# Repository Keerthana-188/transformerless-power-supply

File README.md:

# transformerless-power-supply
This project is a PCB design for a **Transformerless Power Supply** created using KiCad.  
It provides a compact and cost-effective way to power low-current DC circuits directly from AC mains without using bulky transformers.

# Features
Compact PCB layout using through-hole components
- Converts AC to regulated DC using:
  - Capacitor dropper (C4)
  - Full-wave bridge rectifier (D1–D4)
  - Filtering and regulation using LM7805 or LM7812
  - Protection diodes and discharge resistors
  - Indicator LED for output status

## Comparison: Transformerless vs. Conventional Power Supply

| Feature                        | Transformerless Power Supply                        | Conventional Power Supply                            |
|-------------------------------|-----------------------------------------------------|------------------------------------------------------|
| **Size & Weight**             | Very compact and lightweight                        | Bulky due to iron-core transformer                   |
| **Cost**                      | Low cost – fewer and cheaper components             | Higher cost due to transformer and large components  |
| **Efficiency (Low Power Load)** | High for small loads                                 | Moderate (some loss in transformer)                  |
| **Power Output Capacity**     | Suitable only for **low current** applications      | Can provide high current based on transformer rating |
| **Safety**                    | Risky if not handled properly (AC mains exposed)    | Safer due to isolation, especially for beginners     |
| **Applications**              | LED drivers, small control circuits, chargers       | Audio amplifiers, adapters, regulated power supplies |

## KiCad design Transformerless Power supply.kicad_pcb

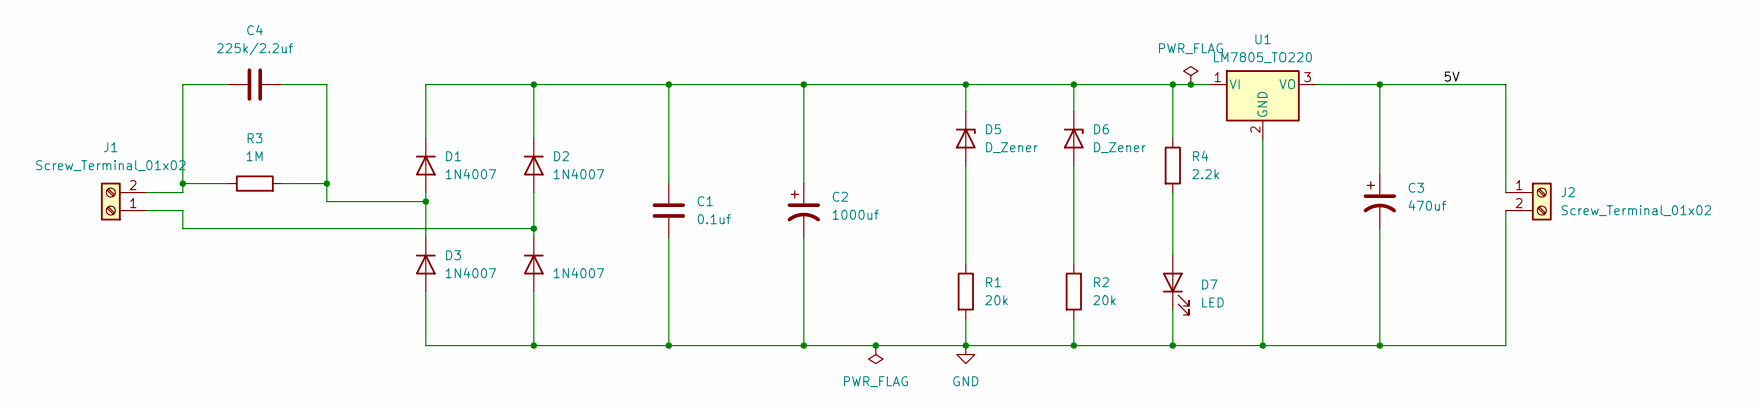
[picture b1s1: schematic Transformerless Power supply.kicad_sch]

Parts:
C1: 0.1uf; C_Disc_D4.7mm_W2.5mm_P5.00mm
C2: 1000uf; CP_Radial_D10.0mm_P5.00mm
C3: 470uf; CP_Radial_D10.0mm_P3.80mm
C4: 225k/2.2uf; C_Rect_L18.0mm_W6.0mm_P15.00mm_FKS3_FKP3
D1, D2, D3, D4: 1N4007; D_DO-41_SOD81_P10.16mm_Horizontal
D5, D6: D_Zener; D_A-405_P7.62mm_Horizontal
D7: LED; LED_D5.0mm
J1, J2: Screw_Terminal_01x02; TerminalBlock_bornier-2_P5.08mm
R1, R2: 20k; R_Axial_DIN0207_L6.3mm_D2.5mm_P7.62mm_Horizontal
R3: 1M; R_Axial_DIN0207_L6.3mm_D2.5mm_P7.62mm_Horizontal
R4: 2.2k; R_Axial_DIN0207_L6.3mm_D2.5mm_P7.62mm_Horizontal
U1: LM7805_TO220; TO-220-3_Vertical

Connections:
/5V: C3.1, J2.1, U1.3 (VO)
GND: C1.2, C2.2, C3.2, D3.2 (A), D4.2 (A), D7.1 (K), J2.2, R1.2, R2.2, U1.2 (GND)
unnamed: C4.2, D1.2 (A), D3.1 (K), R3.2
unnamed: C1.1, C2.1, D1.1 (K), D2.1 (K), D5.1 (K), D6.1 (K), R4.1, U1.1 (VI)
unnamed: D2.2 (A), D4.1 (K), J1.1
unnamed: D5.2 (A), R1.1
unnamed: D6.2 (A), R2.1
unnamed: D7.2 (A), R4.2
unnamed: C4.1, J1.2, R3.1

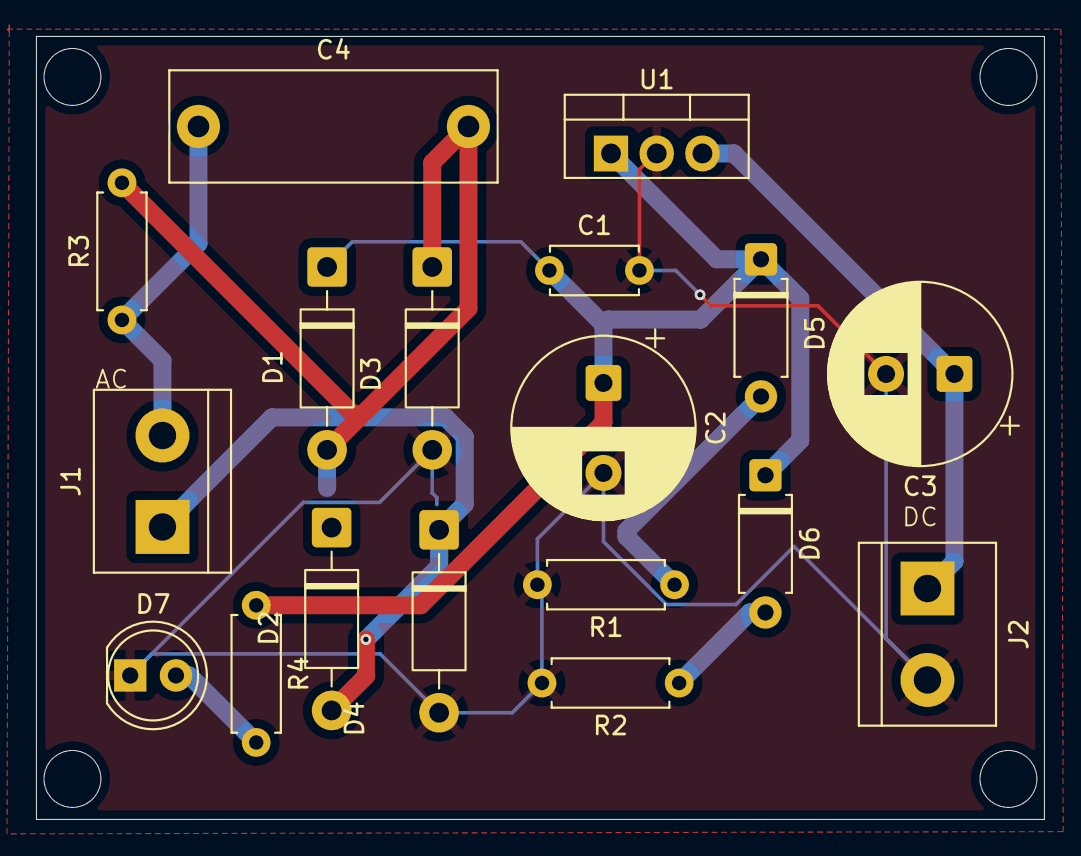
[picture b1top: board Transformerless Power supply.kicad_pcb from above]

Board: 2 copper layers, 56.0 x 43.5 mm, 18 parts (0 on the bottom side), 9 nets.
